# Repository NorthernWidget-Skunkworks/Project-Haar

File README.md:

# Project-Haar

***Mechanical, electrical, and firmware files for a rugged and submersible temperature, pressure, and relative-humidity sensor***

## Namesake and history

***Haar in Ben Bhraggie Woods, Sutherland, Scotland.*** *Photo by Andrew Tryon.*

Project Haar takes its codename from the [North Sea fogs that roll across Britain](https://en.wikipedia.org/wiki/Haar_(fog)).
[Bobby Schulz](https://github.com/bschulz1701) designed it after the consistently-near-0C temperatures and 100% relative humidity of [Chimborazo Volcano](https://en.wikipedia.org/wiki/Chimborazo), Ecuador, claimed the lives of many brave but misguided [BME-280](https://www.adafruit.com/product/2652) units, who then catastrophically bricked their I2C buses and those of their associated data loggers, thus taking down a large fraction of our hydromet network.

Determined to avoid future issues with persistently condensing humidity, we worked to design a unit that would survive in this environment, and indeed, withstand full submersion.

## Technical specifications
<picture>
  <source media="(prefers-color-scheme: dark)" srcset="Documentation/images/Haar_v010_top_annotated_20200427_LIGHT.png">
  <!-- <source media="(prefers-color-scheme: light)" srcset="Documentation/images/Haar_v010_top_annotated_20200427.png"> -->
  
</picture>
<!--  -->

### Electronic Hardware

* Microcontroller (computer) core
  * ATTiny1634
  * [Firmware](Firmware/) written in Arduino-compatible C++
  * Firmware upload via a [0.05" (1.27 mm) pitch 2x3 ICSP header](https://www.digikey.com/product-detail/en/samtec-inc/FTS-103-01-L-D/SAM1156-03-ND/1109979)
* Sensors
  * Relative humidity and temperature sensor: [SHT35-DIS-F2.5KS](https://www.digikey.com/product-detail/en/sensirion-ag/SHT35-DIS-F2.5KS/1649-1067-1-ND/6212138) with [PTFE membrane](https://www.sensirion.com/fileadmin/user_upload/customers/sensirion/Dokumente/2_Humidity_Sensors/Datasheets/Sensirion_Humidity_Sensors_SHT3x_Datasheet_Filter_Membrane.pdf) for water and dust protection
    * Humidity
      * Range: 0--100%
      * Accuracy: ±1.5%
      * Resolution: 0.01%
      * Long-term drift: <0.25%/yr
    * Temperature
      * Range: -40--125 °C
      * Accuracy: ±0.2 °C
      * Resolution: 0.01 °C
      * Long-term drift: <0.01 °C/yr
  * Atmospheric pressure and temperature sensor: [LPS35HW](https://www.st.com/en/mems-and-sensors/lps35hw.html)
    * Pressure
      * Range: 260 to 1260 mbar
      * Accuracy, calibrated: ±1 mbar
      * Accuracy, uncalibrated: ±4 mbar
      * Resolution: 1/4096 mbar (approx. 0.00024 mbar)
    * Temperature
      * Range, full accuracy: 0 to 60 °C
      * Accuracy: ±1.5 °C
      * Resolution: 0.01 °C
* Connections and communications protocols
  * [4-pin "HardMount" plug](https://www.digikey.com/product-detail/en/te-connectivity-amp-connectors/1838893-2/A97650-ND/1764165) ([3D drawing](http://www.te.com/commerce/DocumentDelivery/DDEController?Action=srchrtrv&DocNm=1838893-2&DocType=Customer+View+Model&DocLang=English))
  * I2C
* Power
  * Voltage limits: 3.3V ~ 5.5V
  * Power consumption: 
    * Peak = 5.21mA @ 3.3V
    * Sleep = 0.524 mA @ 3.3V
    * Mean (5 Hz sample rate) = 0.583 mA @ 3.3V
    * Mean (1 Hz sample rate) = 0.780 mA @ 3.3V
* Submersible with its Gore-Tex sealed housing
* Entirely IP67 or greater rated components
* Response Time
  * Temperature: &tau; = 377s
  * Humidity: &tau; = 505s
  * Pressure: &tau; &lt;1s

### Electronic Software and Firmware

* Programmable using the Arduino IDE https://www.arduino.cc/en/main/software
* [Firmware](Firmware/) available in this repository. [`Haar_Firmware.ino`](Firmware/Haar_Firmware/Haar_Firmware.ino) is the standard firmware to be used. 
* [Software](https://github.com/NorthernWidget-Skunkworks/Haar_Library) to use this sensor with Arduino-compatible devices
* Open-source licensing via GNU GPL 3.0

### Weatherproofing and enclosure
* Low-VOC conformal coating as recommended on Page 3 of the [humidity and temperature sensor data sheet](https://www.sensirion.com/fileadmin/user_upload/customers/sensirion/Dokumente/2_Humidity_Sensors/Application_Note/Sensirion_Humidity_Sensors_Handling_Instructions.pdf). We used [Dow Corning 1-2577 Low VOC Conformal Coating](https://www.digikey.com/product-detail/en/1-2577+CONFORMAL+CTG+453G/2275-1-2577CONFORMALCTG453G-ND/11494980/?itemSeq=337863596).
* Fully sealed housing with removable [breathable-membrane (IP68) vent](https://www.digikey.com/product-detail/en/amphenol-ltw/VENT-PS1NGY-O8002/1754-1221-ND/7898276)

> [!WARNING]
> If applying conformal coating, ensure none comes in contact with the sensor orifices themselves, see Senserion Handling Instructions [example](Documentation/images/ConformalApplication.png)

## Assembly

### Sensor circuit board

[Bill of Materials](Production/Haar_HardMount_BoM_0v1.csv)

[PCB Gerber Files](Production/Gerbers_2020-02-20.zip)

Assembling this sensor is possible by hand with sufficient skill and the following tools:
* Temperature-controlled soldering iron
* Hot-air rework station
* Equipment for stenciling with solder paste
* ESD-safe tweezers and workstation
* Solder wick

Many components on this board are fine pitch and/or have difficult to access pads. However, there are not very many components. We would suggest hand assembly using tweezers, stenciled solder paste, and a hot-air rework station. A soldering iron will be helpful -- if not outright essential -- for attaching the "Hard Mount" plug and (if desired) the 2x3 pin ICSP header to upload the firmware.
<!-- >> THOUGHT: I have basic instructions for assembly on the [Project Walrus](https://github.com/NorthernWidget-Skunkworks/Project-TPDH-Walrus) README; I will not reproduce these here just yet, as we might want to set up a separate assembly guide, mostly with good links to existing resources, since our writing something of this nature would be to reinvent the wheel. -->

After finishing the main board assembly, solder the HardMount plug onto the four SMD pads with the notch (for plug orientation) at the bottom side of the board.

### Housing and cabling

Two different housings have been designed to be used in different situations depending on how much robustness is required by the sensor. 
**Closed:**
For maximal robustness a [sealed IP67 rated housing](Mechanical/ClosedBody/ClosedBody.stl) was designed. This housing can be constructed using FDM printing with ABS plastic and acetone smoothing - an [FDM optimized version](Mechanical/ClosedBody_FDM/ClosedBody_FDM.stl) of the design was made featuring an eyelet to hang the enclosure from during the smoothing process. However, results will be significantly better with PA12 SLS nylon - readily available from many print houses.

**Open:**
For maximal responsiveness an [open structure enclosure](Mechanical/OpenBody/OpenBody.stl) was designed to allow airflow while still protecting the sensor from mechanical damage. This enclosure has been tested with FDM and SLA printing, methods will depend on your desired material properties.

#### Parts required

* Sealing plug with cable such as this [-40 degree PVC-jacketed one](https://www.digikey.com/product-detail/en/alpha-wire/AR0400105-SL357/AR0400105SL357-ND/6555497) or [this set of Digi-Key search results for all those that are 3 meters or less in both -40 degree rated PVC and in ](https://www.digikey.com/products/en/cable-assemblies/circular-cable-assemblies/448?k=&pkeyword=&sv=0&pv2331=312745&sf=0&FV=-1%7C216%2C2344%7C346572%2C2346%7C369969%2C2352%7C387800%2C2353%7C421432%2C2380%7C203167%2C-8%7C448%2C77%7C172800%2C77%7C298043%2C77%7C62398&quantity=&ColumnSort=0&page=1&pageSize=25); these come in [a variety of lengths from 0.6 to 20 meters](http://www.alphawire.com/en/Products/Connectivity/AlphaConnect/Cordsets/AR0400105) ([Digi-Key search results](https://www.digikey.com/products/en/cable-assemblies/circular-cable-assemblies/448?FV=2331%7C312745%2C2344%7C346572%2C2350%7C349292%2C2380%7C203167%2C-8%7C448%2C2345%7C1%2C2352%7C387800&quantity=0&ColumnSort=77&page=1&stock=1&rohs=1&nstock=1&k=M12+Alpha+Wire&pageSize=25&pkeyword=M12+Alpha+Wire)). You may also [attach a plug to your own cable](http://www.alphawire.com/en/Products/Connectivity/AlphaConnect/FieldAttachable/200ARS7). Note that I2C communications become iffy for any cable longer than 3 meters.
* [3D-printed housing barrel](Mechanical/ClosedBody_FDM), tapped (see below). We recommend light-colored plastic to reduce radiative heating.
* [4-pin HardMount plug](https://www.digikey.com/product-detail/en/te-connectivity-amp-connectors/1838893-2/A97650-ND/1764165)
* [Amphenol breathable vent](https://www.digikey.com/product-detail/en/amphenol-ltw/VENT-PS1NGY-O8002/1754-1221-ND/7898276)

#### Soldering the HardMount attachment to your board

If it is not already attached, you will need to solder the [4-pin HardMount plug](https://www.digikey.com/product-detail/en/te-connectivity-amp-connectors/1838893-2/A97650-ND/1764165) onto the four SMD pads at the end of the board far from the isolated humidity sensor. You should do so with the notch (for plug orientation) at the bottom side of the board.

Our recommendation for by-hand assembly:
* Add small pillows of solder to each of the four pads, enough to create contact with the HardMount solder cups but not so much that it is not possible to slide the HardMount plug over them.
* Slide the HardMount plug on; it will take a bit of finesse to keep it from being pushed off of the solder pillows.
* Using some Blu Tack (or equivalent), fix the board and HardMount plug in place
* Double-check that the notch in the HardMount plug is on the back side of the board
* Solder on the first connection
* Check whether the board is straight; reflow the solder as needed until the connection is secure
* Solder the second connection
* Flip the board, ensuring that it is straight (if not, make changes)
* Solder the other two solder-cup connections

> [!TIP]
> Sometimes the 3D printed threads are not sufficiently fine to work smoothly. In this case, you can 'repair' the threads using a metal tap. 
>
> The cable side thread is an [M16 x 1.5](https://www.mcmaster.com/26015A263/), and the vent side is a [M12 x 1.5](https://www.mcmaster.com/26015A613/) - More economical taps can be found, these placed here for referance.

#### Cable

Here we assume that you are using [standard Alpha Wire cables with waterproof attachments]([Alpha Wire 5004C](https://www.digikey.com/product-detail/en/alpha-wire/5004C-SL001/5004CSL001-ND/484976). Because of the wire insulation colors available for these cables and the locations of their attachment points to the [4-pin "HardMount" plug](https://www.digikey.com/product-detail/en/te-connectivity-amp-connectors/1838893-2/A97650-ND/1764165) ([3D drawing](http://www.te.com/commerce/DocumentDelivery/DDEController?Action=srchrtrv&DocNm=1838893-2&DocType=Customer+View+Model&DocLang=English)), **our HardMount devices do NOT match standard wire-color definitions (or any kind of standard)**. Wire-color definitions are:

<picture>
  <source media="(prefers-color-scheme: dark)" srcset="Documentation/images/Pinout_LIGHT.png">
  
</picture>

| **Color** | **Connection** |
|-----------|----------------|
| Brown     | V+ (3.3-5.5 V) |
| White     | GND            |
| Black     | SDA            |
| Blue      | SCL            |

For reference, these are the definitions of the four pads to which the [HardMount connector](https://www.digikey.com/product-detail/en/te-connectivity-amp-connectors/1838893-2/A97650-ND/1764165) attaches:
* Top left: SDA
* Top right: SCL
* Bottom left: VCC (3.3V to 5.5V)
* Bottom right: GND

## Firmware

### Downloading and installing the Arduino IDE

Go to https://www.arduino.cc/en/main/software. Choose the proper IDE version for your computer. For Windows, we suggest the non-app version to have more control over Arduino; this might change in the future. You will have to add custom libraries, so the web version will not work (at least, as of the time of writing). Download and install the Arduino IDE. Open it to begin the next steps.

### AVR ISP

To install firmware on the Haar board, you use the [2x3-pin 6-pin ICSP (also called ISP) header](https://www.digikey.com/product-detail/en/samtec-inc/FTS-103-01-L-D/SAM1156-03-ND/1109979) with a special device called an "in-circuit system programmer" (or just "in-system programmer; yup, that's what the acronym stands for).

Many devices exist to upload firmware, including:
* The official [AVR ISP mkII](http://ww1.microchip.com/downloads/en/DeviceDoc/Atmel-42093-AVR-ISP-mkII_UserGuide.pdf) (no longer produced but available used)
* Using an [Arduino as an ISP](https://www.arduino.cc/en/tutorial/arduinoISP)
* The versatile [Olimex AVR-ISP-MK2](https://www.olimex.com/Products/AVR/Programmers/AVR-ISP-MK2/open-source-hardware) (recommended)
* The [Adafruit USBtinyISP](https://www.adafruit.com/product/46)

> [!IMPORTANT] 
> The Haar has a [half-sized (0.05" pitch) ICSP header](https://www.digikey.com/product-detail/en/samtec-inc/FTS-103-01-L-D/SAM1156-03-ND/1109979). Therefore, you will need to have the appropriate 2x3-pin header to form a connection - see detailed [assmbly instructions](Hardware/ISP_Cable_Assembly.md).

<!-- ***Note: Be sure to download and/or update drivers for your ISP.*** -->

> [!NOTE]
> Frequently on Windows machines the driver configuration of the ISP programmer can become problematic. See discussion of how to get drivers and the use of Zadig to configure them in this [Sparkfun Guide](https://learn.sparkfun.com/tutorials/pocket-avr-programmer-hookup-guide/installing-drivers)

### Uploading the firmware

Using this ISP, upload (as of the time of writing): [the Arduino sketch in this folder](Firmware/Haar_Firmware/). To do so, follow these steps:

1. Open the Arduino IDE.
2. Follow [these instructions](https://github.com/SpenceKonde/ATTinyCore/blob/master/Installation.md) to install the [ATTinyCore board definitions](https://github.com/SpenceKonde/ATTinyCore)
3. Select [ATTiny1634](https://github.com/SpenceKonde/ATTinyCore/blob/master/avr/extras/ATtiny_1634.md) **(No bootloader)**

> [!CAUTION]
> Check your ISP target voltage before you connect! Make sure the target voltage is set to 3.3v, 5v can damage the sensor irreparably 

4. Plug your ISP of choice into your computer (via a USB cable) and onto the 6-pin header. There are two ways to place it on; the header is aligned such that the ribbon cable should be facing away from the board while programming. If this fails without being able to upload, try flipping the header around. This should both power the board and provide communications.
5. Go to Tools --> Programmer and select the appropriate programmer based on what you are using.
6. Go to Tools --> Burn Bootloader. Yes, we know that you just selected "ATTiny1634 (No bootloader)", but this step sets the fuses, which configure their internal oscillator and brown-out detection.
7. Go to Sketch --> Upload Using Programmer. After several seconds, you learn whether you succeeded or failed. Hopefully it worked!

***Uploading using the in-system programmer.***

> [!NOTE] 
> **Linux Users:** You must supply permissions to the Arduino IDE for it to be able to use the ICSP, or you will have to run it using `sudo`. The former option is better; the latter is easier in the moment.

## Register map and firmware internals

The Haar firmware runs on an ATTiny1634 and exposes an I2C register map to the host logger. The default I2C address is `0x42`.

The device exposes a flat, byte-addressable virtual address space. The master writes a 1-byte starting address, then reads up to 32 bytes in one transaction. Pages are 32-byte aligned.

Two layouts exist: the **current firmware** (deployed) and the **proposed** layout under [NW-Device-Specification](https://github.com/NorthernWidget/NW-Device-Specification) Schema 1, which the firmware will be updated to implement.

### Current register map (deployed firmware)

10-byte array, no schema byte, no device name. The library reads one register at a time (no bulk page read). The master triggers a conversion by writing `0x01` to address `0x00`; the firmware clears bit 0 when the measurement is complete.

```
0x00        Config       bit 0 = sample trigger (master writes 1; cleared when done)
0x01        —            unused
0x02–0x03   Temp LPS35HW int16, raw (library: val/100.0 → °C)
0x04–0x05   Temp SHT31   uint16, raw SHT31 counts (library: -45 + 175×val/65535 → °C)
0x06–0x08   Pressure     24-bit, raw LPS35HW counts (library: val/4096.0 → hPa)
0x09–0x0A   Humidity     uint16, raw SHT31 counts (library: 100×val/65535 → % RH)
             ⚠ 0x0A is out of bounds — Reg[10] ends at 0x09
```

### Proposed register map (NW-Device-Specification Schema 1)

Two 32-byte pages. Identity is EEPROM-backed; sensor data is SRAM-backed. No calibration page (both sensors are factory-calibrated with no user calibration step).

**Page 0 (0x00–0x1F) — Identity (EEPROM)**

```
Block 0 (0x00–0x07)   Core identity
  0x00        0x01              Schema (NW-Device-Specification v1)
  0x01–0x04   'H','a','a','r'   Device name (ASCII)
  0x05–0x07   0x00,0x00,0x00    Null padding

Block 1 (0x08–0x0F)   Version
  0x08        HW major
  0x09        HW minor
  0x0A        FW patch          (NW combined-repo convention)
  0x0B–0x0D   0x00,0x00,0x00    Unused (combined repo)
  0x0E–0x0F   0x00,0x00         Reserved

Block 2 (0x10–0x17)   Serial number
  0x10–0x11   0x48,0x01         Board type ('H' = 0x48, revision index 1)
  0x12–0x13   [manufacture]     Group ID
  0x14–0x15   [manufacture]     Unique ID
  0x16–0x17   0x00,0x00         FirmwareID (legacy, reserved)

Block 3 (0x18–0x1F)   Integrity + administration
  0x18–0x1C   0x00 ×5           Reserved
  0x1D        0x00              Magic byte (reserved; purpose TBD)
  0x1E        [computed]        CRC-8 of bytes 0x00–0x1D
  0x1F        0x42              I2C address (writable; 0xFF = use default)
```

**Page 1 (0x20–0x3F) — Sensor data (SRAM)**

```
Block 0 (0x20–0x27)   SHT31 — temperature + humidity
  0x20        Status       bit 0=ready, bit 1=SHT31 fault, bit 2=LPS35HW fault,
                           bit 7=pan-fault
  0x21        Extended faults (reserved, 0x00)
  0x22–0x23   Temp SHT31   int16, 0.01 °C, little-endian
  0x24–0x25   Humidity     uint16, 0.01 % RH, little-endian
  0x26–0x27   Reserved

Block 1 (0x28–0x2F)   LPS35HW — pressure + temperature
  0x28–0x2B   Pressure     uint32, 0.01 hPa, little-endian
  0x2C–0x2D   Temp LPS35HW int16, 0.01 °C, little-endian
  0x2E–0x2F   Reserved

Block 2–3 (0x30–0x3F)   Reserved
```

Check bit 0 of 0x20 before using any measurement. If clear, all other Page 1 bytes are stale.

---

## Writing a program to connect to the Haar sensor

Once the  is bootloaded and connected with a LiDAR Lite sensor, you should be able to use any standard Arduino device to connect to it and read its data.

### Very simple Arduino code

This code is intended for any generic Arduino system.

```c++
// Include the Haar library
#include "Haar.h"

// Declare variables -- just as strings
String header;
String data;

// Instantiate class
Haar myTPRH;

void setup(){
    // Begin Serial connection to computer at 38400 baud
    Serial.begin(38400);
    // Obtain the header just once
    header = myTPRH.getHeader();
    // Print the header to the serial monitor
    Serial.println(header);
}

void loop(){
    // Take one reading every (10 + time to take reading) seconds
    // and print it to the screen
    myTPRH.updateMeasurements();
    data = myTPRH.getString();
    Serial.println(data);
    delay(10000); // Wait 10 seconds before the next reading, inefficiently
}
```

### Northern Widget Margay code

The [Margay data logger](github.com/NorthernWidget-Skunkworks/Project-Margay) is the lightweight and low-power open-source data-logging option from Northern Widget. It saves data to a local SD card and includes on-board status measurements and a low-drift real-time clock. We have written [a library to interface with the Margay](github.com/NorthernWidget-Skunkworks/Margay_Library), which can in turn be used to link the Margay with sensors.

```c++
// Include the libraries
#include "Margay.h"
#include "Haar.h"

// Declare variables -- just as strings
String header;
String data;

// Instantiate classes
Haar myTPRH;
Margay Logger; // Margay v2.2; UPDATE CODE TO INDICATE THIS

// Empty header to start; will include sensor labels and information
String Header = "";

// I2CVals for Haar
uint8_t I2CVals[] = {0x42}; // DEFAULT

//Number of seconds between readings
uint32_t updateRate = 60;

void setup(){
    Header = Header + myTPRH.getHeader();
    Logger.begin(I2CVals, sizeof(I2CVals), Header);
    initialize();
}

void loop(){
    initialize();
    Logger.run(update, updateRate);
}

String update() {
    initialize();
    return myTPRH.getString();
}

void initialize(){
    myTPRH.begin();
}
```

### Northern Widget Okapi code

>> Currently nearly identical to Margay code, by design. Add telemetry with Particle Boron.

```c++
// Include the libraries
#include "Okapi.h"
#include "Haar.h"

// Declare variables -- just as strings
String header;
String data;

// Instantiate classes
Haar myTPRH;
Okapi Logger;

// Empty header to start; will include sensor labels and information
String Header = "";

// I2CVals for Haar
uint8_t I2CVals[] = {0x42}; // DEFAULT

//Number of seconds between readings
uint32_t updateRate = 60;

void setup(){
    Header = Header + myTPRH.getHeader();
    Logger.begin(I2CVals, sizeof(I2CVals), Header);
    initialize();
}

void loop(){
    initialize();
    Logger.run(update, updateRate);
}

String update() {
    initialize();
    return myTPRH.getString();
}

void initialize(){
    myTPRH.begin();
}
```

## Characterization

### Response time

<!-- 

***Response-time testing.*** *Our initial tests demonstrate that, with the vent detached, the Haar exhibits sensitivity and response time similar to the [T9602 temperature and relative humidity sensor](https://www.amphenol-sensors.com/images/stories/moisture-humidity/main-T9602-Mod-4.png). With the vent cap on, this response is dampened significantly.* -->
This sensor was tested for using an impulse for each variable (temperature, pressure, humidity) and for each housing type (closed, open). The details of each of these evaluations can be found in the testing documentation: [Temperature](Testing/Temperature/README.md), [Pressure](Testing/Pressure/README.md), [Humidity](Testing/Humidity/README.md). A summary of these results, along with visuals of the step response, is presented here.

Approximate time to equilibrium for each variable and sensor type
| **Sensor** | Temperature | Pressure | Humidity | 
|---:|:---:|:---:|:---:|
| Control | 105s | &lt;1s | 18 min |
| Haar, Closed | 75s | &lt;1s | 31.75 min |
| Haar, Open | 12.5 min | &lt;1s | 10.25 min |

This response time information should serve as a guide to the choice of housing. In situations where very fast response time is required *and* the sensor will not be subjected to environmental extremes (e.g. in a radiation shield on a meteorological station) an open housing can be used. However, in cases where the hazards of the environment are a priority (e.g. a sensor in the flood plane of a river to calibrate a depth sensor) a closed housing should be used.

<!-- >> @bschulz1701: Application note about when to use the cap? Notes about the IP ratings of the devices and practical ratings as well? And I've been looking for a M12 vent without any membrane so it can still physically protect the sensor (or act as a roof for rain) but have not yet found one. Thoughts on this?
>> @awickert: The cap would desire to be used when there is the potential for the device to become fully submerged and slow response time is not a problem (for getting system averages instead of response time or quick variance). All elements of the device (uncapped) are rated to >IP67, however, the conformal coating of the board is not specifically rated for any pressure. It would likely survive breif immersion but not for extended periods of time. As for the a cap with no membrane: since be 3D print the body, we would just design a body with a "roof" instead of a thread at the top, and holes or slots in the side, whichever we desire. Then instead of replacing the end cap, you just replace the entire body (which just screws on to the bottom). This would actually make it a bit easier to make, since it would be one less thread that would need to be made by hand. -->

## NW-Device-Specification — Schema 1, Page 0

Implements [NW-Device-Specification](https://github.com/NorthernWidget/NW-Device-Specification) Schema 1. The 32-byte identity block (Page 0) is stored at the top of EEPROM:

```
Block 0:  Schema=0x01, Name='H','a','a','r',0x00,0x00,0x00
Block 1:  HW major=[mfr], HW minor=[mfr], FW patch=[mfr], 0x00,0x00,0x00, Reserved
Block 2:  Board type=0x4801 ('H'=0x48, rev 1), Group ID=[mfr], Unique ID=[mfr], FirmwareID=0x0000
Block 3:  Reserved, Magic=0x00, CRC=[computed], I2C address=0x48
```

Legacy deployed units use I²C address `0x42` (pre-Schema-1).

## Acknowledgments

Support for this project provided by:

<br/>
<br/>

<br/>
<br/>
<br />This work is licensed under a <a rel="license" href="http://creativecommons.org/licenses/by-sa/4.0/">Creative Commons Attribution-ShareAlike 4.0 International License</a>.

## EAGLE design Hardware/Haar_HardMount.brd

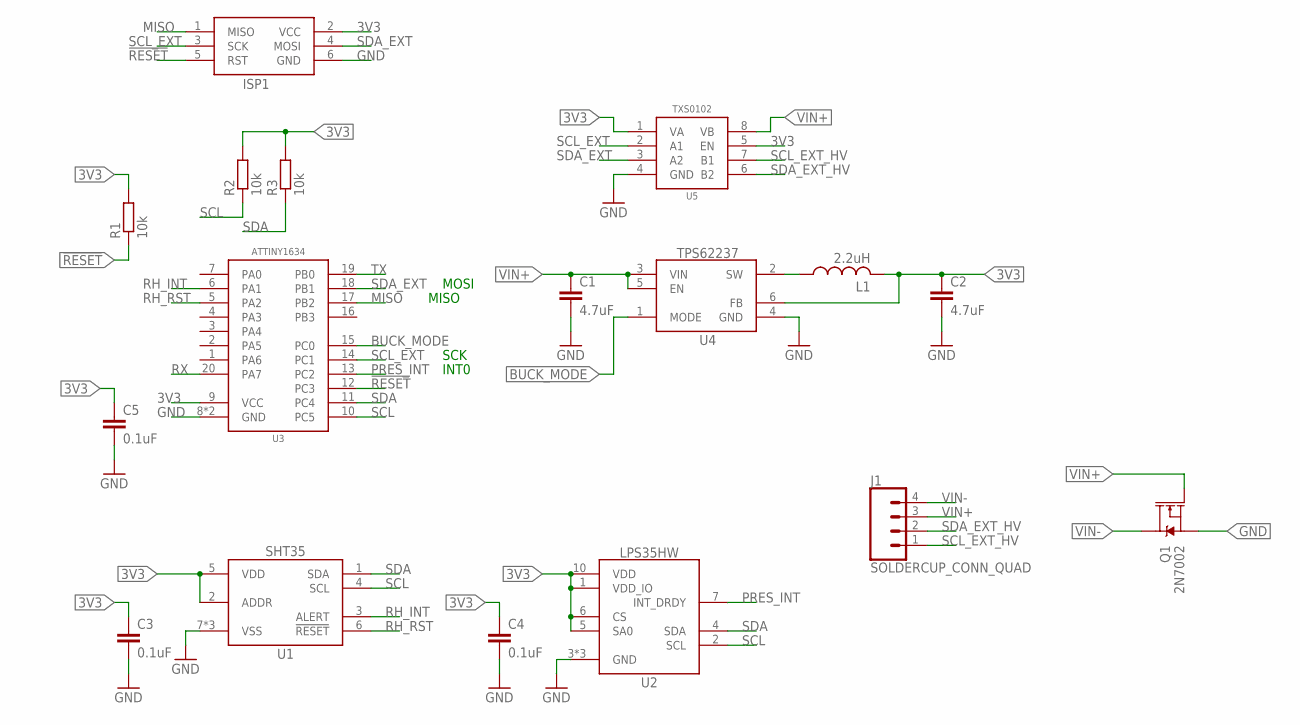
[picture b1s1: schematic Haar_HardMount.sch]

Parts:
C1, C2: 4.7uF; C0402; MPN GRM155R61A475MEAAD; DIGIKEY 490-14306-1-ND
C3, C4, C5: 0.1uF; C0402
ISP1: AVRISP1.27MM; 2X3_1.27
J1: SOLDERCUP_CONN_QUAD
L1: 2.2uH; 0805; MPN 74479775222; DIGIKEY 732-2953-1-ND
Q1: 2N7002; SOT323
R1, R2, R3: 10k; R0402
U1: SHT35DFN; DFN_8_2.5X2.5
U2: LPS35HW; CCLGA10L
U3: ATTINY1634QFN; QFN20
U4: TPS62237DRY; DRY0006A
U5: TXS0102DQM; DQM_R-PX2SON-N8

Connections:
3V3: C2.1, C3.1, C4.1, C5.1, ISP1.2 (VCC), L1.2, R1.2, R2.2, R3.2, U1.2 (ADDR), U1.5 (VDD), U2.1 (VDD_IO), U2.5 (SA0), U2.6 (CS), U2.10 (VDD), U3.9 (VCC), U4.6 (FB), U5.1 (VA), U5.5 (EN)
!RESET: ISP1.5 (RST), R1.1, U3.12 (PC3)
BUCK_MODE: U3.15 (PC0), U4.1 (MODE)
GND: C1.2, C2.2, C3.2, C4.2, C5.2, ISP1.6 (GND), Q1.2 (S), U1.7 (VSS), U1.8 (VSS), U1.EP (VSS), U2.3 (GND), U2.8 (GND), U2.9 (GND), U3.8 (GND), U3.EP (GND), U4.4 (GND), U5.4 (GND)
MISO: ISP1.1 (MISO), U3.17 (PB2)
unnamed: L1.1, U4.2 (SW)
PRES_INT: U2.7 (INT_DRDY), U3.13 (PC2)
RH_INT: U1.3 (ALERT), U3.6 (PA1)
RH_RST: U1.6 (!RESET), U3.5 (PA2)
RX: U3.20 (PA7)
SCL: R2.1, U1.4 (SCL), U2.2 (SCL), U3.10 (PC5)
SCL_EXT: ISP1.3 (SCK), U3.14 (PC1), U5.2 (A1)
SCL_EXT_HV: J1.1, U5.7 (B1)
SDA: R3.1, U1.1 (SDA), U2.4 (SDA), U3.11 (PC4)
SDA_EXT: ISP1.4 (MOSI), U3.18 (PB1), U5.3 (A2)
SDA_EXT_HV: J1.2, U5.6 (B2)
TX: U3.19 (PB0)
VIN+: C1.1, J1.3, Q1.1 (G), U4.3 (VIN), U4.5 (EN), U5.8 (VB)
VIN-: J1.4, Q1.3 (D)

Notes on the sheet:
MOSI
MISO
SCK
INT0

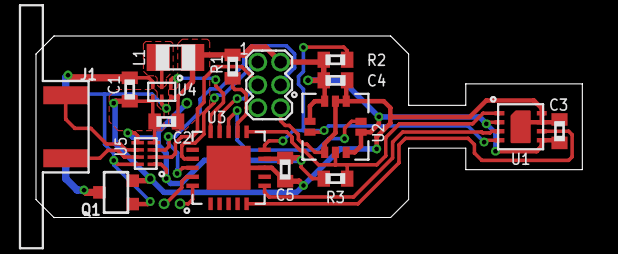
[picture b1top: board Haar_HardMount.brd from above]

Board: 2 copper layers, 30.4 x 10.1 mm, 17 parts (0 on the bottom side), 17 nets.

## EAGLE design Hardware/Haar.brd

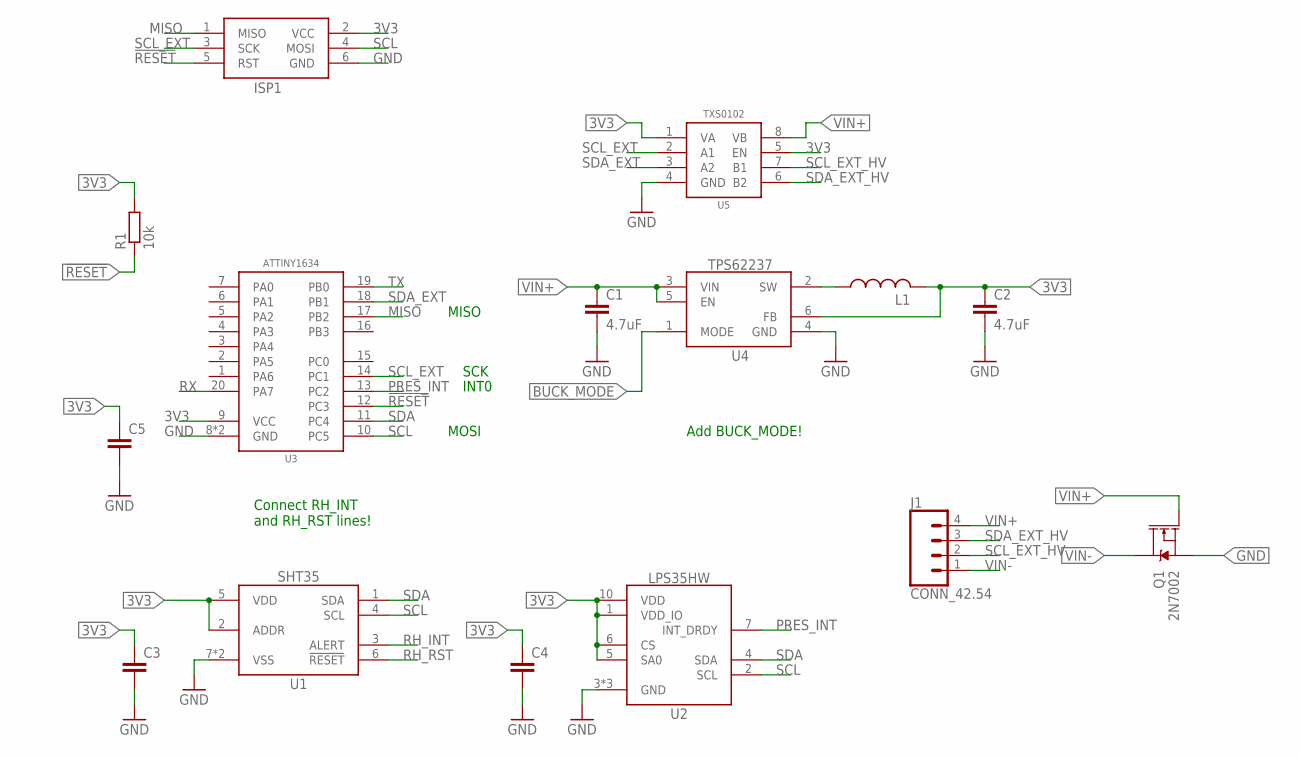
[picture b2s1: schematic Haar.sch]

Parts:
C1, C2: 4.7uF; C0402
C3, C4, C5: C-EU0.1UFC0402; C0402
ISP1: AVRISP1.27MM; 2X3_1.27
J1: CONN_42.54; 1X04
L1: INDUCTOR0805; 0805
Q1: 2N7002; SOT323
R1: 10k; R0402
U1: SHT35DFN; DFN_8_2.5X2.5
U2: LPS35HW; CCLGA10L
U3: ATTINY1634QFN; QFN20
U4: TPS62237DRY; DRY0006A
U5: TXS0102DQM; DQM_R-PX2SON-N8

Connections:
3V3: C2.1, C3.1, C4.1, C5.1, ISP1.2 (VCC), L1.2, R1.2, U1.2 (ADDR), U1.5 (VDD), U2.1 (VDD_IO), U2.5 (SA0), U2.6 (CS), U2.10 (VDD), U3.9 (VCC), U4.6 (FB), U5.1 (VA), U5.5 (EN)
!RESET: ISP1.5 (RST), R1.1, U3.12 (PC3)
BUCK_MODE: U4.1 (MODE)
GND: C1.2, C2.2, C3.2, C4.2, C5.2, ISP1.6 (GND), Q1.2 (S), U1.7 (VSS), U1.8 (VSS), U2.3 (GND), U2.8 (GND), U2.9 (GND), U3.8 (GND), U3.EP (GND), U4.4 (GND), U5.4 (GND)
MISO: ISP1.1 (MISO), U3.17 (PB2)
unnamed: L1.1, U4.2 (SW)
PRES_INT: U2.7 (INT_DRDY), U3.13 (PC2)
RH_INT: U1.3 (ALERT)
RH_RST: U1.6 (!RESET)
RX: U3.20 (PA7)
SCL: ISP1.4 (MOSI), U1.4 (SCL), U2.2 (SCL), U3.10 (PC5)
SCL_EXT: ISP1.3 (SCK), U3.14 (PC1), U5.2 (A1)
SCL_EXT_HV: J1.2, U5.7 (B1)
SDA: U1.1 (SDA), U2.4 (SDA), U3.11 (PC4)
SDA_EXT: U3.18 (PB1), U5.3 (A2)
SDA_EXT_HV: J1.3, U5.6 (B2)
TX: U3.19 (PB0)
VIN+: C1.1, J1.4, Q1.1 (G), U4.3 (VIN), U4.5 (EN), U5.8 (VB)
VIN-: J1.1, Q1.3 (D)

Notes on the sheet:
MOSI
MISO
SCK
INT0
Connect RH_INT and RH_RST lines!
Add BUCK_MODE!

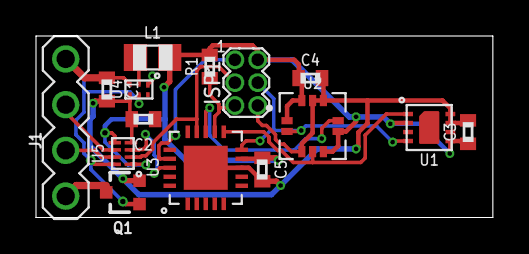
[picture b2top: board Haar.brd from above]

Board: 2 copper layers, 25.4 x 10.1 mm, 15 parts (0 on the bottom side), 14 nets.

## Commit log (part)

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2019-03-26 Added licence
2019-03-26 Fixed name
2019-03-27 Initial layout and schematic
    First cut schematic and layout, needs additional logic lines added on schematic and general layout improvement
2019-03-27 Added HardMount version, improved layout on conventional version
2019-04-19 Fixed ISP error, updated notes
    Fixed an errant connection to the ISP header on both versions in schematic, still need to fix the layout. Also removed outdated notes on schematic
2019-04-21 Reroute; dimensions
2019-04-22 Fixed routing, cleaned up, ready for fab
    Minor routing fixes, added some silkscreen, generated gerbers, ready for prototype fab
2019-04-25 Generated Gerbers, ready to fab
2019-04-26 Minor dimensional cleanup, final gerbers generated
    Fixed dimensional alignment, generated gerbers, sent to fab
2019-06-13 Updated part values, added prelim firmware
    Added values to parts for full BoM generation, added preliminary test firmware, consolidation and streamlining to come, simply proof of functionality at the moment
2019-06-14 Added ALPHA test interface
    Testing and library integration required for interface
2019-06-26 Updates and testing of test interface
    Continued development of test interface, verified functional with Margay v2.2 and added pullups on Haar v0.0
2019-06-27 Beveled corners on board
2019-07-02 Minor cleanup on board, fixed #1, sent v0.1 to fab
    Minor board cleanup, added pullup resistors on internal I2C lines, fixed #1 issue
2019-08-08 Minor improvements to increase speed of startup and reliability
    Increased startup speed by removing some delays, added additional deep sleep mode, need to add support for this via I2C, used lighter sleep mode for normal operation, continual testing required to re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
2020-02-20 Generated fab quote
    Updated part values for inductor and capacitor in Eagle, generated new BoM and zipped into file for quote generation
2020-04-26 rm old Gerbers; see prior releases
2020-04-30 images and solid works
2020-04-30 Schematic images for upcoming README updates
2020-04-30 Housing main cylinder
2020-05-07 First pass full documentation
2020-05-07 Annotated board photo
2020-05-24 connections: not included in BoM CSV (board only)
2020-05-24 0.05" pitch ICSP header
2020-05-25 Housing, ICSP power
2020-05-25 Firmware: ATTinyCore
2020-05-25 ICSP header 0.05" link
2020-05-25 Firmware section heading
2020-05-25 bootloader --> firmware
2020-05-26 Vent information
2020-05-26 Test results from @bschulz1701
2020-05-28 Updated comment on readme - use of membrane cap
    Added note for the use of the membrane cap along with an alternative design for a more open air design for less extreme environments
2020-05-29 #2: Firmware and test softwre with READMEs per @bschulz1701
2020-06-01 Add 3D model link for HardMount plug
2020-06-02 AlphaWire links
2020-06-02 Upload Using Programmer image: point to Symbiont-LiDAR
2020-06-02 Housing and now-detailed cabling into Assembly section
2020-06-04 Fix: #include "Haar" --> #include "Haar.h"
2020-06-04 examples: function capitalization; semicolon
2020-06-04 init() seems to be a protected function name; use initialize() instead
2020-06-04 Example: rm parens in Resnik Logger();
2020-06-18 Sources of support
2020-06-18 Remove blank line between images
2020-08-06 Symbiont --> Haar; VCC/GND cable colors flipped (FIXED!)
2020-08-07 Default ADR to 0x42
2020-08-08 HardMount plug: solder attachment, wiring
2020-08-08 "Bootloader" for setting fuses
2020-08-10 Input range 3.3V to 5.5V
2020-09-08 Low VOC conformal coating links
2020-09-08 Cable length / I2C warning (3 m)
2020-09-08 Cables: multiple materials and lengths
2020-09-08 Link to only those cables with all 4 positions loaded
2020-09-28 Added dimensional drawings
2021-03-02 DOI badge
2021-07-18 run/margay logger code example cleanup
2021-07-19 ISP driver note
2021-07-19 shift resnik to okapi
2021-07-22 small spelling change
2021-07-23 quote change
2021-08-08 note consistency changes
2021-08-08 note consistency changes pt. 2
2023-10-26 Added first iteration of testing documentation
2023-10-26 Minor formatting fixes to testing docs
2023-10-26 Added data analysis code
    Added analysis code and outputs for pressure, temp and RH testing
2023-10-26 Fixed link for temp analysis docs
2023-10-26 Fixed pressure doc linkage
2023-10-26 More name fixing...
2023-10-26 Removed leading row of CSV for format
2024-08-21 Extensive documentation updates
    - Updates to data used in temp and RH testing
    - Updates to the testing apparatus for temp testing.
    - Added PID controller code
    - Added code for control sensor
    - Many documentation updates in main readme
    - Added methods on construction of mini ICSP cable
2024-08-22 Fixed naming of images in temperature README
2024-08-22 Link updates in README
2024-08-22 Added grey `TempBoxDimensions` graphic
    Added grey version of graphic as 'universal' option until issue of dark/light mode detection is worked out
2024-08-22 Added step response graphs, mechanical pinout graphic
    - Added step response graphs
    - Added all mechanical parts
    - Added renders of mechanical parts
    - Added Pinout graphic
2024-08-27 Adjusted folders, added production documents
    Added BoM, added frame to Eagle schematic, moved production files into own folder, renamed folder to `Software`, and moved old design to `legacy` folder.
2024-11-02 Added documentation and mechanical parts

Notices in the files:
parts and their libraries:
bschulz: This work is licensed under the Creative Commons Attribution-ShareAlike 4.0
